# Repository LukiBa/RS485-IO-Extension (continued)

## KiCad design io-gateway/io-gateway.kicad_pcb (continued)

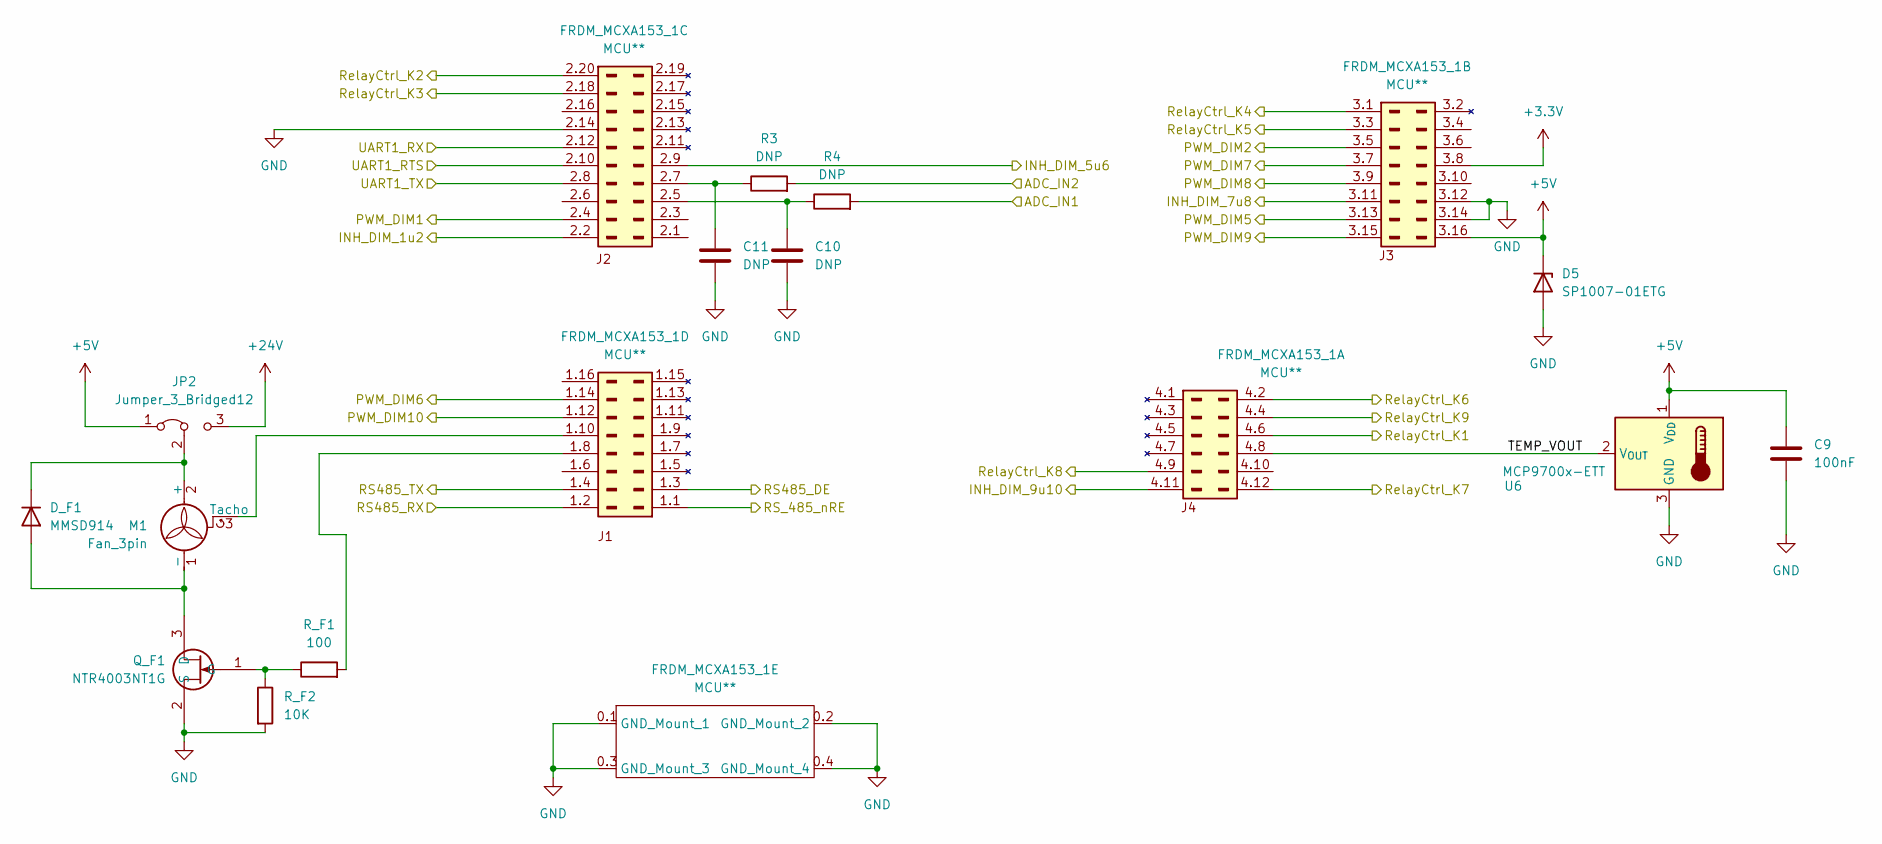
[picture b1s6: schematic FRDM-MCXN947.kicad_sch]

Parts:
C9: 100nF; C_0603_1608Metric_Pad1.08x0.95mm_HandSolder
C10, C11: DNP; C_0603_1608Metric_Pad1.08x0.95mm_HandSolder
D5: SP1007-01ETG; D_SOD-882D
D_F1: MMSD914; D_SOD-123
FRDM_MCXA153_1: MCU**; FRDM-MCXA153-SMD
JP2: Jumper_3_Bridged12; PinHeader_1x03_P2.54mm_Vertical
M1: Fan_3pin; FanPinHeader_1x03_P2.54mm_Vertical
Q_F1: NTR4003NT1G; SOT-23-3; Mouser Part Number 863-NTR4003NT1G
R3, R4: DNP; R_0603_1608Metric_Pad0.98x0.95mm_HandSolder
R_F1: 100; R_0603_1608Metric_Pad0.98x0.95mm_HandSolder
R_F2: 10K; R_0603_1608Metric_Pad0.98x0.95mm_HandSolder
U6: MCP9700x-ETT; SOT-23

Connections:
+3.3V: FRDM_MCXA153_1.3.8 (Pin_J3_3V3_Out); also elsewhere on the board
+5V: C9.1, D5.1 (K), FRDM_MCXA153_1.3.16 (Pin_J3_16_VIN), JP2.1 (A), U6.1 (V_{DD}); also elsewhere on the board
+24V: JP2.3 (B); also elsewhere on the board
/ADC_IN1: R4.2; also elsewhere on the board
/ADC_IN2: R3.2; also elsewhere on the board
/FRDM-MCXA153/RS485_DE: FRDM_MCXA153_1.1.3 (Pin_J1_3); also elsewhere on the board
/FRDM-MCXA153/RS485_RX: FRDM_MCXA153_1.1.2 (Pin_J1_2); also elsewhere on the board
/FRDM-MCXA153/RS485_TX: FRDM_MCXA153_1.1.4 (Pin_J1_4); also elsewhere on the board
/FRDM-MCXA153/RS_485_nRE: FRDM_MCXA153_1.1.1 (Pin_J1_1); also elsewhere on the board
/FRDM-MCXA153/TEMP_VOUT: FRDM_MCXA153_1.4.8 (Pin_8), U6.2 (V_{OUT})
/INH_DIM_1u2: FRDM_MCXA153_1.2.2 (Pin_J2_2); also elsewhere on the board
/INH_DIM_5u6: FRDM_MCXA153_1.2.9 (Pin_J2_9); also elsewhere on the board
/INH_DIM_7u8: FRDM_MCXA153_1.3.11 (Pin_J3_11); also elsewhere on the board
/INH_DIM_9u10: FRDM_MCXA153_1.4.11 (Pin_11); also elsewhere on the board
/PWM_DIM1: FRDM_MCXA153_1.2.4 (Pin_J2_4); also elsewhere on the board
/PWM_DIM2: FRDM_MCXA153_1.3.5 (Pin_J3_5); also elsewhere on the board
/PWM_DIM5: FRDM_MCXA153_1.3.13 (Pin_J3_13); also elsewhere on the board
/PWM_DIM6: FRDM_MCXA153_1.1.14 (Pin_J1_14); also elsewhere on the board
/PWM_DIM7: FRDM_MCXA153_1.3.7 (Pin_J3_7); also elsewhere on the board
/PWM_DIM8: FRDM_MCXA153_1.3.9 (Pin_J3_9); also elsewhere on the board
/PWM_DIM9: FRDM_MCXA153_1.3.15 (Pin_J3_15); also elsewhere on the board
/PWM_DIM10: FRDM_MCXA153_1.1.12 (Pin_J1_12); also elsewhere on the board
/RelayCtrl_K1: FRDM_MCXA153_1.4.6 (Pin_6); also elsewhere on the board
/RelayCtrl_K2: FRDM_MCXA153_1.2.20 (Pin_J2_20); also elsewhere on the board
/RelayCtrl_K3: FRDM_MCXA153_1.2.18 (Pin_J2_18); also elsewhere on the board
/RelayCtrl_K4: FRDM_MCXA153_1.3.1 (Pin_J3_1); also elsewhere on the board
/RelayCtrl_K5: FRDM_MCXA153_1.3.3 (Pin_J3_3); also elsewhere on the board
/RelayCtrl_K6: FRDM_MCXA153_1.4.2 (Pin_2); also elsewhere on the board
/RelayCtrl_K7: FRDM_MCXA153_1.4.12 (Pin_12); also elsewhere on the board
/RelayCtrl_K8: FRDM_MCXA153_1.4.9 (Pin_9); also elsewhere on the board
/RelayCtrl_K9: FRDM_MCXA153_1.4.4 (Pin_4); also elsewhere on the board
/UART1_RTS: FRDM_MCXA153_1.2.10 (Pin_J2_10); also elsewhere on the board
/UART1_RX: FRDM_MCXA153_1.2.12 (Pin_J2_12); also elsewhere on the board
/UART1_TX: FRDM_MCXA153_1.2.8 (Pin_J2_8); also elsewhere on the board
GND: C9.2, C10.2, C11.2, D5.2 (A), FRDM_MCXA153_1.0.1 (GND_Mount_1), FRDM_MCXA153_1.0.2 (GND_Mount_2), FRDM_MCXA153_1.0.3 (GND_Mount_3), FRDM_MCXA153_1.0.4 (GND_Mount_4), FRDM_MCXA153_1.2.14 (GND), FRDM_MCXA153_1.3.12 (Pin_J3_12_GND), FRDM_MCXA153_1.3.14 (Pin_J3_14_GND), Q_F1.2 (S), R_F2.2, U6.3 (GND); also elsewhere on the board
unnamed: D_F1.2 (A), M1.1 (-), Q_F1.3 (D)
unnamed: D_F1.1 (K), JP2.2 (C), M1.2 (+)
unnamed: C10.1, FRDM_MCXA153_1.2.5 (Pin_J2_5), R4.1
unnamed: C11.1, FRDM_MCXA153_1.2.7 (Pin_J2_7), R3.1
unnamed: FRDM_MCXA153_1.1.8 (Pin_J1_8), R_F1.2
unnamed: FRDM_MCXA153_1.1.10 (Pin_J1_10), M1.3 (Tacho)
unnamed: Q_F1.1 (G), R_F1.1, R_F2.1

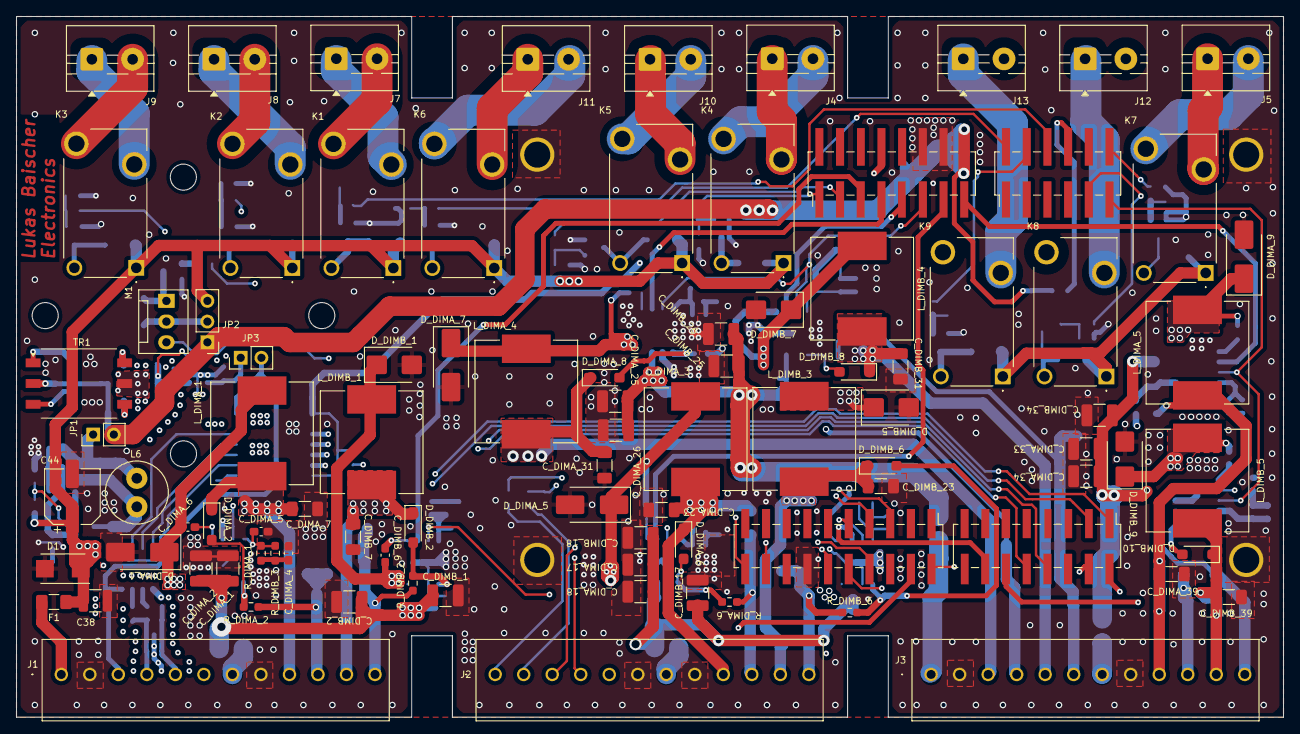
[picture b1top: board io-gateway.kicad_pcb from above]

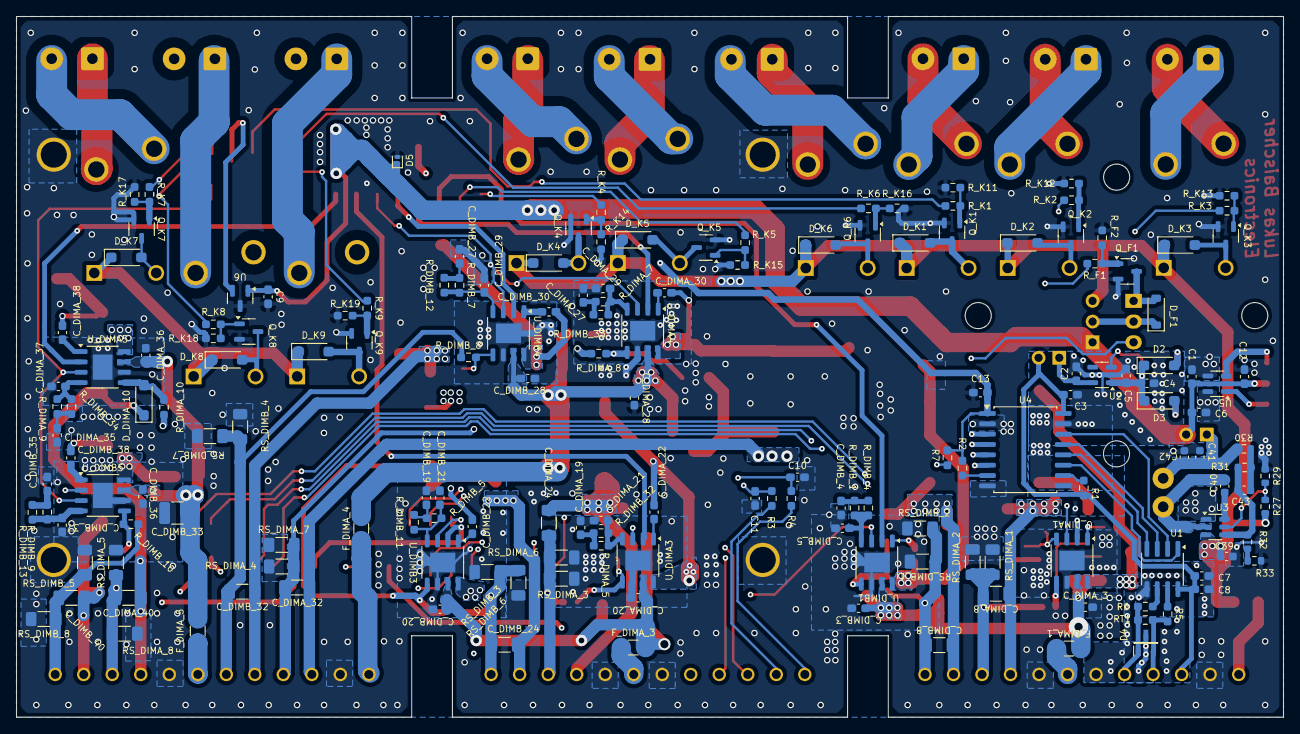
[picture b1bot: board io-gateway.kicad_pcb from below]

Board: 4 copper layers, 155.5 x 86.0 mm, 254 parts (166 on the bottom side), 168 nets.

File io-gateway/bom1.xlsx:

Id | Designator | Footprint | Quantity | Designation | Unit Price | Quantitiy for 10 Pics | Quantitiy ordered | Overall Price | Mouser link
1 | C_DIMA_2,C_DIMA_18,C_DIMA_34,C_DIMB_17,C_DIMB_1,C_DIMA_26,C_DIMA_33,C_DIMA_17,C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 | C_1210_3225Metric | 17 | 10µF 100V | 0.39900000000000002 | 170 | 17 | 6.7830000000000004 | GRM32EC72A106ME05K Murata Electronics | Mouser Österreich
2 | D_DIMB_1,D_DIMA_7,D_DIMB_7,D_DIMA_9,D_DIMA_5,D_DIMB_5,D_DIMB_9,D_DIMA_1 | D_SMB | 8 | STPS3L60UF | 0.14199999999999999 | 80 | 100 | 14.2 | STPS3L60UF STMicroelectronics | Mouser Österreich
3 | K9,K7,K8,K4,K3,K6,K2,K5,K1 | 20715562 | 9 | 2071556-2 | 1.24 | 90 | 10 | 12.4 | 2071556-2 TE Connectivity | Mouser Österreich
4 | D1 | DIOM5436X244N | 1 | SMBJ28A | 0.152 | 10 | 10 | 1.52 | SMBJ28A Bourns | Mouser Österreich
5 | C44 | CP_Elec_6.3x5.4 | 1 | 47µF | 0 | 10 | 0 | 0 | Auf Lager
6 | C_DIMA_7,C_DIMB_23,C_DIMA_39,C_DIMB_31,C_DIMB_39,C_DIMB_7,C_DIMA_23,C_DIMA_31 | C_1206_3216Metric | 8 | 1 µF 100V | 4.2000000000000003E-2 | 80 | 100 | 4.2 | CL31B105KCHNNNE Samsung Electro-Mechanics | Mouser Österreich
7 | J1,J3,J2 | 1752201 | 3 | 1752201 | 12.94 | 30 | 9 | 116.46 | 1311011 Phoenix Contact | Boxes, Enclosures, Racks | DigiKey
8 | D_K8,D_F1,D_K7,D_K1,D_K9,D_K3,D_K4,D_K2,D_K6,D_K5 | D_SOD-123 | 10 | MMSD914 | 4.2000000000000003E-2 | 100 | 110 | 4.62 | https://www.mouser.at/ProductDetail/onsemi/MMSD914T1G?qs=P4I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
9 | D_DIMA_2,D_DIMA_8,D_DIMB_2,D_DIMB_6,D_DIMB_10,D_DIMB_8,D_DIMA_6,D_DIMA_10 | D_SOD-123 | 8 | MMSZ39T1G | 3.3000000000000002E-2 | 80 | 100 | 4.9400000000000004 | https://www.mouser.at/ProductDetail/863-MMSZ39T1G | BZT52-B68J Nexperia | Mouser Österreich
10 | C_DIMA_5,C_DIMA_37,C_DIMA_29,C_DIMB_21,C_DIMB_29,C_DIMB_37,C_DIMB_5,C_DIMA_21 | C_0603_1608Metric | 8 | 22pF | 2.4E-2 | 80 | 100 | 2.4 | 06035C220JAT2A KYOCERA AVX | Mouser Österreich
11 | J5,J7,J4,J13,J10,J12,J11,J9,J8 | TerminalBlock_MaiXu_MX126-5.0-02P_1x02_P5.00mm | 9 | 1-282836-3 | 0.54600000000000004 | 90 | 100 | 54.6 | 1-282836-3 TE Connectivity | Mouser Österreich
12 | L_DIMB_5,L_DIMB_4,L_DIMB_1,L_DIMA_1,L_DIMA_4,L_DIMA_3,L_DIMA_5,L_DIMB_3 | L_12x12mm_H8mm | 8 | 47µH 3.8A | 0.495 | 80 | 100 | 49.5 | IFDC5050JZER470M Vishay / Dale | Mouser Österreich
13 | U5 | SOT-23-5 | 1 | SN6501DBVR | 1.33 | 10 | 1 | 1.33 | SN6501DBVR Texas Instruments | Mouser Österreich
14 | F1 | Fuse_0603_1608Metric | 1 | Fuse | 0.28999999999999998 | 10 | 15 | 4.3499999999999996 | 0ABB-1000-TM Bel Fuse | Mouser Österreich
15 | C1,C9,C3,C8,C5 | C_0603_1608Metric | 5 | 100nF | 0 | 50 | 0 | 0 | Auf Lager
16 | R29,R31 | R_0603_1608Metric | 10 | 100k | 3.5000000000000003E-2 | 100 | 100 | 3.5000000000000004 | https://www.mouser.at/ProductDetail/Vishay-Draloric/RCA06031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
17 | R_DIMB_2,R_DIMA_2,R_DIMB_6,R_DIMA_6,R_DIMA_8,R_DIMB_10,R_DIMB_8,R_DIMA_10 | R_0603_1608Metric | 8 | 47k | 7.0000000000000001E-3 | 80 | 100 | 0.70000000000000007 | CRCW060347K0JNEAC Vishay | Mouser Österreich
18 | R_DIMA_1,R_DIMB_5,R_DIMA_7,R_DIMB_7,R_DIMA_9,R_DIMB_1,R_DIMA_5,R_DIMB_9 | R_0603_1608Metric | 8 | 33k | 3.0000000000000001E-3 | 80 | 100 | 0.3 | CR0603-JW-333ELF Bourns | Mouser Österreich
19 | C_DIMA_6,C_DIMB_6,C_DIMA_36,C_DIMB_30,C_DIMA_22,C_DIMA_30,C_DIMA_20,C_DIMB_28,C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 | C_0603_1608Metric | 18 | 100nF 100V | 8.0000000000000002E-3 | 180 | 200 | 1.6 | CL10B104KC8NNNC Samsung Electro-Mechanics | Mouser Österreich
20 | C6,C7,C2,C4 | C_0603_1608Metric | 4 | 10µF | 2.8000000000000001E-2 | 40 | 100 | 2.8000000000000003 | LMK107BBJ106MALT TAIYO YUDEN | Mouser Österreich
21 | L6 | L_Radial_D7.5mm_P3.50mm_Fastron_07P | 1 | 10µH | 0.69299999999999995 | 10 | 10 | 6.93 | DR0608-103L Coilcraft | Mouser Österreich
22 | TR1 | Transformer_Wuerth_750315371 | 1 | Wuerth_750315371 | 2.11 | 10 | 1 | 2.11 | 750315371 Wurth Elektronik | Mouser Österreich
23 | R2,R1 | R_0603_1608Metric | 2 | 4k7 | 5.0000000000000001E-3 | 20 | 100 | 0.5 | CR0603-JW-472ELF Bourns | Mouser Österreich
24 | R27 | R_0603_1608Metric | 1 | 470k | 8.0000000000000002E-3 | 10 | 100 | 0.8 | https://www.mouser.at/ProductDetail/YAGEO/RC0603FR-07470KP?q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
25 | C_DIMA_4,C_DIMB_27,C_DIMA_27,C_DIMB_19,C_DIMA_35,C_DIMB_4,C_DIMB_35,C_DIMA_19 | C_0603_1608Metric | 8 | 470pF | 2.7E-2 | 80 | 100 | 2.7 | https://www.mouser.at/ProductDetail/Murata-Electronics/GCM18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
26 | R_K8,R_F1,R_K6,R_K4,R_K3,R_K2,R_K9,R_K1,R_K7,R_K5 | R_0603_1608Metric | 10 | 100R | 6.0000000000000001E-3 | 100 | 120 | 0.72 | AC0603JR-07100RL YAGEO | Mouser Österreich
27 | M1 | FanPinHeader_1x03_P2.54mm_Vertical | 1 | Fan_3pin | 0.16300000000000001 | 10 | 10 | 1.6300000000000001 | 22-23-2031 Molex | Mouser Österreich
28 | FRDM_MCXA153_1 | FRDM-MCXA153-SMD | 1 | MCU** | 12.75 | 10 | 2 | 25.5 | FRDM-MCXA153 NXP Semiconductors | Mouser Österreich
29 | Q_K8,Q_K2,Q_F1,Q_K7,Q_K4,Q_K3,Q_K1,Q_K5,Q_K6,Q_K9 | SOT-23-3 | 10 | NTR4003NT1G | 3.6999999999999998E-2 | 100 | 100 | 3.6999999999999997 | NTR4003NT1G onsemi | Mouser Österreich
30 | U_DIMA4,U_DIMB1,U_DIMB4,U_DIMB5,U_DIMA3,U_DIMA5,U_DIMA1,U_DIMB3 | HSOP-8-1EP_3.9x4.9mm_P1.27mm_EP2.41x3.1mm | 8 | LED5000PHR | 1.39 | 80 | 10 | 13.899999999999999 | LED5000PHR STMicroelectronics | Mouser Österreich
31 | U6 | SOT-23 | 1 | MCP9700T-E/LT | 0.34399999999999997 | 10 | 2 | 0.68799999999999994 | MCP9700T-E/LT Microchip Technology | Mouser Österreich
32 | C41,C42 | C_0603_1608Metric | 2 | 22µF | 0 | 20 | 0 | 0 | Auf Lager
33 | U3 | SOT-23-6 | 1 | TPS54308 | 0.745 | 10 | 10 | 7.45 | TPS54308DDCR Texas Instruments | Mouser Österreich
34 | RS_DIMB_5,RS_DIMB_1,RS_DIMB_4,RS_DIMA_4,RS_DIMB_3,RS_DIMA_5,RS_DIMA_1,RS_DIMA_3 | R_1206_3216Metric | 8 | NM | 0.47 | 80 | 50 | 23.5 | AC1206FR-7W1RL YAGEO | Mouser Österreich | RCWE1206R500FKEA Vishay / Dale | Mouser Österreich | RCWE1206R250FKEA Vishay / Dale | Mouser Österreich
35 | C_DIMB_8,C_DIMA_40,C_DIMA_32,C_DIMB_40,C_DIMA_8,C_DIMB_32,C_DIMA_24,C_DIMB_24 | C_1206_3216Metric | 8 | NM | 0 | 80 | 0 | 0 | Not mounted
36 | U4 | SOIC-16W_7.5x10.3mm_P1.27mm | 1 | ISO7741 | 2.42 | 10 | 10 | 24.2 | ISO7742FTBDWRQ1 Texas Instruments | Mouser Österreich
37 | R4,R3 | R_0603_1608Metric | 2 | NM | 0 | 20 | 0 | 0 | Reserve
38 | D2,D3 | D_SOD-123 | 2 | MBR0520 | 0.114 | 20 | 20 | 2.2800000000000002 | MBR0520-TP Micro Commercial Components (MCC) | Mouser Österreich
39 | R33 | R_0603_1608Metric | 1 | 3k3 | 0 | 10 | 0 | 0 | Auf Lager
40 | R32 | R_0603_1608Metric | 1 | 10k | 0 | 10 | 0 | 0 | Auf Lager
41 | C10,C11 | C_0603_1608Metric | 2 | NM | 0 | 20 | 0 | 0 | Reserve
42 | U1 | SOIC-8_3.9x4.9mm_P1.27mm | 1 | SN65LBC176QDR | 2.33 | 10 | 1 | 2.33 | SN65LBC176QDRQ1 Texas Instruments | Mouser Österreich
43 | C43 | C_0603_1608Metric | 1 | 75pF | 3.5999999999999997E-2 | 10 | 0 | 0 | Auf Lager
44 | R30 | R_0603_1608Metric | 1 | 49.9R | 0 | 10 | 0 | 0 | Auf Lager
45 | U2 | SOT-23-5 | 1 | TPS76350 | 0.69899999999999995 | 10 | 10 | 6.9899999999999993 | TPS76350DBVT Texas Instruments | Mouser Österreich
46 | MCU J2 | PinHeader 2x20 P2.54 SMD Vertical | 1 |  | 2.98 | 10 | 2 | 5.96 | https://www.mouser.at/ProductDetail/200-HW1011FD610SM
47 | MCU J1 + J3 | PinHeader 2x16 P2.54 SMD Vertical | 2 |  | 2.98 | 20 | 2 | 5.96 | https://www.mouser.at/ProductDetail/200-HW1011FD610SM
48 | MCU J4 | PinHeader 2x12 P2.54 SMD Vertical | 1 |  | 2.98 | 10 | 1 | 2.98 | https://www.mouser.at/ProductDetail/200-HW1011FD610SM
 |  |  |  |  |  |  |  | 424.05099999999993
 |  |  |  |  |  |  |  | 307.59099999999995

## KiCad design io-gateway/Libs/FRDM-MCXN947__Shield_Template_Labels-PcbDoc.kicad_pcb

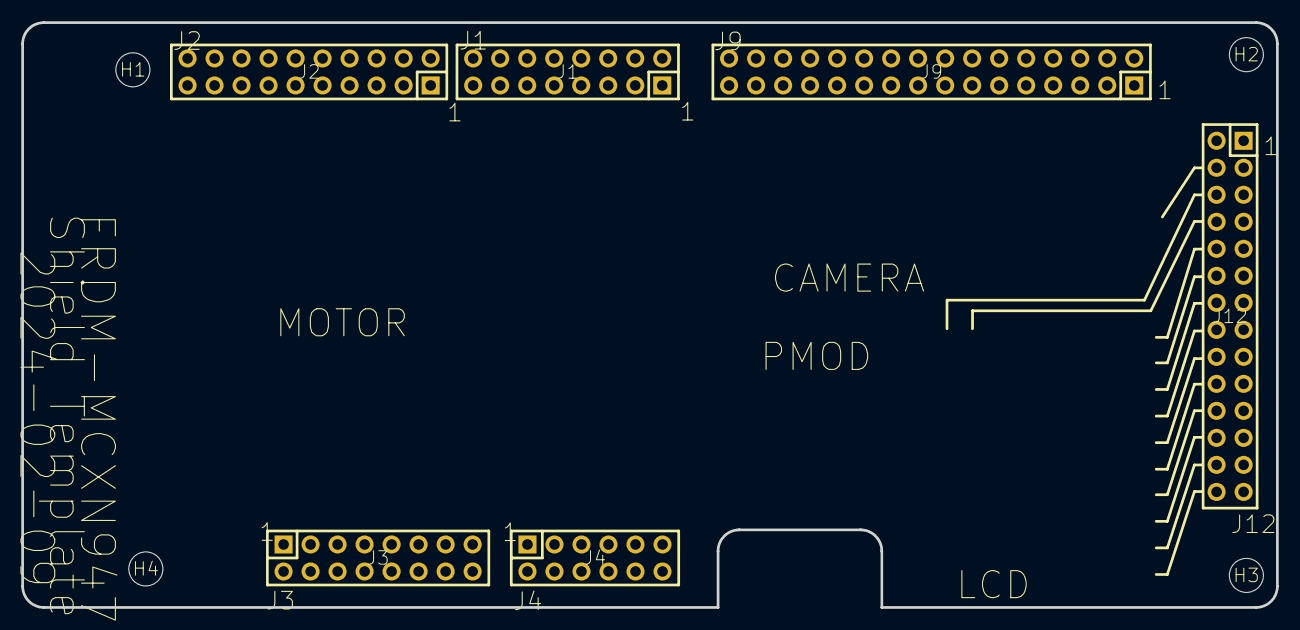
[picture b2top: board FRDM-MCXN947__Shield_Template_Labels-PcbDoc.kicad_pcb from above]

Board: 2 copper layers, 118.0 x 55.0 mm, 10 parts (0 on the bottom side), 2 nets.

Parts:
H1: H1; MOUNTINGHOLE_3.2MM_M3
H2: H2; MOUNTINGHOLE_3.2MM_M3
H3: H3; MOUNTINGHOLE_3.2MM_M3
H4: H4; MOUNTINGHOLE_3.2MM_M3
J1: J1; SSQ-108-03-T-D
J2: J2; SSQ-110-03-T-D
J3: J3; SSQ-108-03-T-D
J4: J4; SSQ-106-03-T-D
J9: J9; SSQ-116-03-T-D
J12: J12; SSQ-114-03-T-D

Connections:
+3v3: J3.4, J3.8, J9.21, J12.1
GND: J2.14, J3.12, J3.14, J9.22, J12.2

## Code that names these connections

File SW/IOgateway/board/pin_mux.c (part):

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processor_version: 25.06.10
external_user_signals: {}
pin_labels:
- {pin_num: '44', pin_signal: P3_6/CLKOUT/LPSPI1_PCS3/PWM0_A0/FREQME_CLK_OUT1, label: PWM_DIM7}
- {pin_num: '43', pin_signal: P3_7/TRIG_IN2/LPSPI1_PCS2/PWM0_B0, label: PWM_DIM3}
- {pin_num: '41', pin_signal: P3_9/TRIG_IN4/LPSPI1_SDI/LPUART1_TXD/CT_INP5/PWM0_B1, label: PWM_DIM6}
- {pin_num: '40', pin_signal: P3_10/TRIG_IN5/LPSPI1_SCK/LPUART1_RTS_B/CT1_MAT0/PWM0_A2, label: PWM_DIM5}
- {pin_num: '39', pin_signal: P3_11/WUU0_IN24/TRIG_IN6/LPSPI1_PCS0/LPUART1_CTS_B/CT1_MAT1/PWM0_B2, label: PWM_DIM2}
- {pin_num: '38', pin_signal: P3_12/LPUART2_RTS_B/CT1_MAT2/PWM0_X0, label: PWM_DIM8}
- {pin_num: '37', pin_signal: P3_13/LPUART2_CTS_B/CT1_MAT3/PWM0_X1, label: PWM_DIM4}
- {pin_num: '36', pin_signal: P3_14/WUU0_IN25/LPUART2_RXD/CT_INP6/PWM0_X2, label: PWM_DIM1}
- {pin_num: '35', pin_signal: P3_15/LPUART2_TXD/CT_INP7, label: INH_DIM_1u2, identifier: INH_DIM_1u2}
- {pin_num: '32', pin_signal: P3_29/WUU0_IN27/ISPMODE_N/CT_INP3/ADC0_A14, label: INH_DIM_7u8, identifier: INH_DIM_7u8}
- {pin_num: '17', pin_signal: P2_3/WUU0_IN19/TRIG_IN7/LPUART0_CTS_B/LPUART2_RXD/CT_INP13/CT2_MAT3/ADC0_A2/CMP1_IN0, label: ADC_IN1, identifier: ADC_IN1}
- {pin_num: '16', pin_signal: P2_2/TRIG_IN6/LPUART0_RTS_B/LPUART2_TXD/CT_INP12/CT2_MAT2/ADC0_A4/CMP0_IN0, label: INH_DIM_3u4, identifier: INH_DIM_3u4}
- {pin_num: '15', pin_signal: P2_1/TRIG_IN7/LPUART0_TXD/CT_INP17/CT2_MAT1/ADC0_A1, label: ADC_IN2, identifier: ADC_IN2}
- {pin_num: '14', pin_signal: P2_0/WUU0_IN18/TRIG_IN6/LPUART0_RXD/CT_INP16/CT2_MAT0/ADC0_A0, label: PCB_Temperature, identifier: PCB_Temperature}
- {pin_num: '42', pin_signal: P3_8/WUU0_IN23/TRIG_IN3/LPSPI1_SDO/LPUART1_RXD/CT_INP4/PWM0_A1/CLKOUT, label: INH_DIM_5u6, identifier: INH_DIM_5u6}
- {pin_num: '1', pin_signal: P1_7/WUU0_IN9/TRIG_OUT2/LPUART2_CTS_B/CT_INP7/ADC0_A23, label: RS485_nRE, identifier: RS485_nRE}
- {pin_num: '64', pin_signal: P1_6/TRIG_IN2/LPSPI0_PCS1/LPUART2_RTS_B/CT_INP6/ADC0_A22, label: RS485_DE, identifier: RS485_DE}
- {pin_num: '3', pin_signal: P1_9/LPUART1_TXD/LPI2C0_SCL/CT_INP9/CT0_MAT3/I3C0_SCL, label: Relay_K2, identifier: Relay_K2}
- {pin_num: '2', pin_signal: P1_8/WUU0_IN10/LPUART1_RXD/LPI2C0_SDA/CT_INP8/CT0_MAT2/I3C0_SDA, label: Relay_K3, identifier: Relay_K3}
- {pin_num: '21', pin_signal: P2_7/TRIG_IN5/CT_INP19/CT1_MAT3/VREFI/ADC0_A7, label: Relay_K4, identifier: Relay_K4}
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
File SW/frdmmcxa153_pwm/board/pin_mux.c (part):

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mcu_data: ksdk2_0
processor_version: 25.06.10
pin_labels:
- {pin_num: '44', pin_signal: P3_6/CLKOUT/LPSPI1_PCS3/PWM0_A0/FREQME_CLK_OUT1, label: PWM_DIM9, identifier: PWM_DIM9}
- {pin_num: '43', pin_signal: P3_7/TRIG_IN2/LPSPI1_PCS2/PWM0_B0, label: PWM_DIM5, identifier: PWM_DIM5}
- {pin_num: '42', pin_signal: P3_8/WUU0_IN23/TRIG_IN3/LPSPI1_SDO/LPUART1_RXD/CT_INP4/PWM0_A1/CLKOUT, label: INH_DIM_7u8, identifier: INH_DIM_7u8}
- {pin_num: '41', pin_signal: P3_9/TRIG_IN4/LPSPI1_SDI/LPUART1_TXD/CT_INP5/PWM0_B1, label: PWM_DIM8, identifier: PWM_DIM8}
- {pin_num: '40', pin_signal: P3_10/TRIG_IN5/LPSPI1_SCK/LPUART1_RTS_B/CT1_MAT0/PWM0_A2, label: PWM_DIM7, identifier: PWM_DIM7}
- {pin_num: '39', pin_signal: P3_11/WUU0_IN24/TRIG_IN6/LPSPI1_PCS0/LPUART1_CTS_B/CT1_MAT1/PWM0_B2, label: PWM_DIM2, identifier: PWM_DIM2}
- {pin_num: '36', pin_signal: P3_14/WUU0_IN25/LPUART2_RXD/CT_INP6/PWM0_X2, label: PWM_DIM1, identifier: PWM_DIM1}
- {pin_num: '37', pin_signal: P3_13/LPUART2_CTS_B/CT1_MAT3/PWM0_X1, label: PWM_DIM6, identifier: PWM_DIM6}
- {pin_num: '38', pin_signal: P3_12/LPUART2_RTS_B/CT1_MAT2/PWM0_X0, label: PWM_DIM10, identifier: PWM_DIM10}
- {pin_num: '35', pin_signal: P3_15/LPUART2_TXD/CT_INP7, label: INH_DIM_1u2, identifier: INH_DIM_1u2}
 * BE CAREFUL MODIFYING THIS COMMENT - IT IS YAML SETTINGS FOR TOOLS ***********
 */
/* clang-format on */
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         /* Invert Input: Does not invert. */
         | PORT_PCR_INV(PCR_INV_inv0));

    const port_pin_config_t PWM_DIM7 = {/* Internal pull-up/down resistor is disabled */
                                        .pullSelect = kPORT_PullDisable,
                                        /* Low internal pull resistor value is selected. */
                                        .pullValueSelect = kPORT_LowPullResistor,
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                                        /* Pin Control Register fields [15:0] are not locked */
                                        .lockRegister = kPORT_UnlockRegister};
    /* PORT3_10 (pin 40) is configured as PWM0_A2 */
    PORT_SetPinConfig(BOARD_PWM_DIM7_PORT, BOARD_PWM_DIM7_PIN, &PWM_DIM7);

    /* PORT3_11 (pin 39) is configured as PWM0_B2 */
    PORT_SetPinMux(BOARD_PWM_DIM2_PORT, BOARD_PWM_DIM2_PIN, kPORT_MuxAlt5);
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                      /* Input Buffer Enable: Enables. */
                      | PORT_PCR_IBE(PCR_IBE_ibe1));

    const port_pin_config_t PWM_DIM9 = {/* Internal pull-up/down resistor is disabled */
                                        .pullSelect = kPORT_PullDisable,
                                        /* Low internal pull resistor value is selected. */
                                        .pullValueSelect = kPORT_LowPullResistor,
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                                        /* Pin Control Register fields [15:0] are not locked */
                                        .lockRegister = kPORT_UnlockRegister};
    /* PORT3_6 (pin 44) is configured as PWM0_A0 */
    PORT_SetPinConfig(BOARD_PWM_DIM9_PORT, BOARD_PWM_DIM9_PIN, &PWM_DIM9);

    const port_pin_config_t PWM_DIM5 = {/* Internal pull-up/down resistor is disabled */
                                        .pullSelect = kPORT_PullDisable,
                                        /* Low internal pull resistor value is selected. */
                                        .pullValueSelect = kPORT_LowPullResistor,
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                                        /* Pin Control Register fields [15:0] are not locked */
                                        .lockRegister = kPORT_UnlockRegister};
    /* PORT3_7 (pin 43) is configured as PWM0_B0 */
    PORT_SetPinConfig(BOARD_PWM_DIM5_PORT, BOARD_PWM_DIM5_PIN, &PWM_DIM5);

    /* PORT3_8 (pin 42) is configured as P3_8 */
    PORT_SetPinMux(BOARD_INH_DIM_7u8_PORT, BOARD_INH_DIM_7u8_PIN, kPORT_MuxAlt0);
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
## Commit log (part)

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2025-07-24 schematic init
2025-07-24 temp commit
2025-07-25 buck regulator schematic ready
2025-07-25 buck regulator ready
2025-07-27 PCB Settings
2025-07-27 daily
2025-07-28 add some datasheets
2025-08-01 add Terminal Blocks
2025-08-07 Label Terminal Block Pins
2025-08-07 add relays
2025-08-08 add frdm-mcxn947 lib
2025-08-08 start creating FRDM lib
2025-08-08 complete prev commit
2025-08-11 update mcu lib
2025-08-14 Place Relays
2025-08-26 add dimmer
2025-09-01 layout for first dimmer
2025-09-03 add second dimmer
2025-09-04 add voltage regulator
2025-09-05 temp
2025-09-05 reannotate dimmers and relays
2025-09-05 duplicate dimmer
2025-09-08 Place some Relays
2025-09-08 fix some drc issues
2025-09-08 Connect some Relays
2025-09-09 all dimmers placed
2025-09-10 Change Holes to Vias
2025-09-12 connect Relays in Schematics
2025-09-15 add RS485
2025-09-16 upd rs485
2025-09-16 connect rs485
2025-09-22 connect all relays
2025-09-22 connect inh pins
2025-09-23 improve ground connections
2025-09-25 remove 2 Dimmer
2025-10-09 gen gerbers
2025-10-13 fix minor issues
2025-10-15 order V1.0
2025-10-20 add first test sw
2025-11-13 increase Pads for Handsolder, fix issue with rectifier
2025-11-13 add fuses to Dimmer VIN
2025-11-18 first test with queue
2025-11-23 add pwm example with 8 PWMs
2025-11-24 UART with DMA and FreeRTOS
2025-11-26 add relay ctrl
2025-12-05 Add ESD protection for RS485
2025-12-08 add new transformer
2025-12-11 V1.2
